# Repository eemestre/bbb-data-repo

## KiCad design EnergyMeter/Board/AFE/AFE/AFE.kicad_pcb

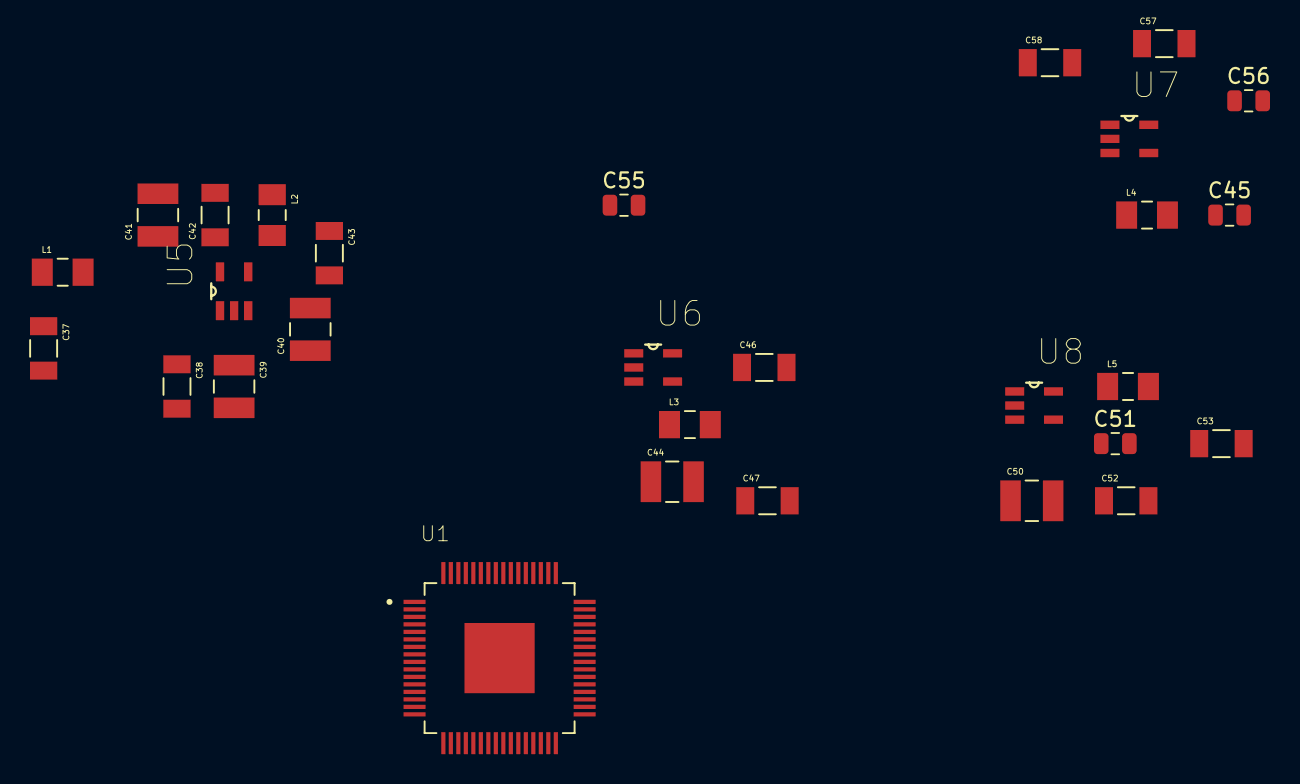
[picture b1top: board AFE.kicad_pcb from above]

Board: 2 copper layers, 29 parts (0 on the bottom side), 13 nets, no tracks yet.

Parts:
C37, C38, C42, C43, C46, C47, C52, C53, C57, C58: 10UF; CAPC3216X180N
C39, C40, C41, C44, C50: 1UF; CAPC3225X210N
C45, C51, C55, C56: 2.2UF; C_0805_2012Metric
L1, L2, L3, L4, L5: 470UH; BEADC3216X180N
U1: ADC; QFP50P1200X1200X120-65N
U5: TPS60403DBVT; SOT95P280X145-5N
U6: TPS73230DBVT; SOT95P280X145-5N
U7: TPS72301DBVT; SOT95P280X145-5N
U8: TPS73201DBVT; SOT95P280X145-5N

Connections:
+5V: C37.1, L1.1
GNDA: C37.2, C38.2, C39.2, C41.2, C42.2, C43.2, C44.2, C45.2, C46.2, C47.2, C51.2, C52.2, C53.2, C55.2, C56.2, C57.2, C58.2, U5.4, U6.2, U7.1, U8.2
unnamed: C38.1, C39.1, C44.1, C50.1, L1.2, U5.2, U6.1, U6.3, U8.1, U8.3
unnamed: C40.1, U5.3
unnamed: C40.2, U5.5
unnamed: C41.1, C42.1, L2.1, U5.1
unnamed: C45.1, C46.1, L3.1, U6.5
unnamed: C51.1, C52.1, L5.1, U8.5
unnamed: C56.1, C57.1, L4.1
TP4: C43.1, C55.1, L2.2, U7.2, U7.3
TP5: C47.1, L3.2
TP6: C58.1, L4.2
TP13: C53.1, L5.2

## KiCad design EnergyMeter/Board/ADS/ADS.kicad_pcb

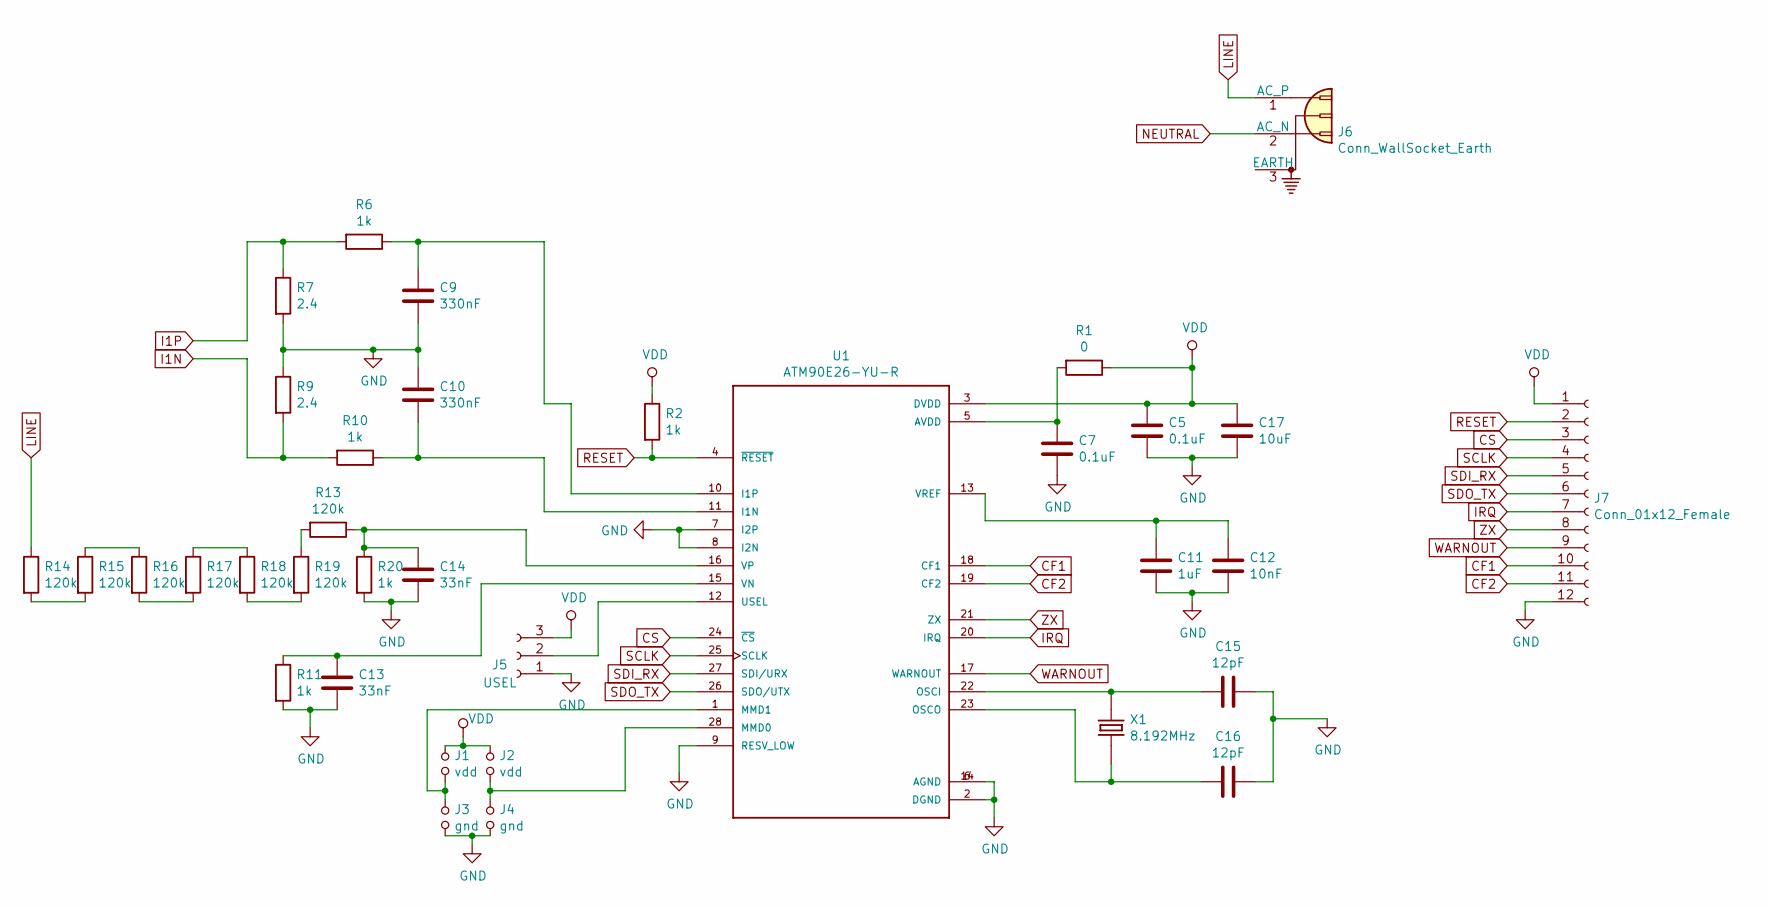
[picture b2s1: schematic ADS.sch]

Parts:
C5, C7: 0.1uF; C_0603_1608Metric
C9, C10: 330nF; C_0603_1608Metric
C11: 1uF; C_0603_1608Metric
C12: 10nF; C_0603_1608Metric
C13, C14: 33nF; C_0603_1608Metric
C15, C16: 12pF; C_0603_1608Metric
C17: 10uF; C_0603_1608Metric
J1, J2: vdd; PinHeader_1x02_P2.54mm_Vertical
J3, J4: gnd; PinHeader_1x02_P2.54mm_Vertical
J5: USEL; PinHeader_1x03_P2.54mm_Vertical
J6: Conn_WallSocket_Earth
J7: Conn_01x12_Female; PinHeader_1x12_P2.54mm_Vertical
R1: 0; R_0603_1608Metric
R2, R6, R10, R11, R20: 1k; R_0603_1608Metric
R7, R9: 2.4; R_0603_1608Metric
R13, R14, R15, R16, R17, R18, R19: 120k; R_0805_2012Metric
U1: ATM90E26-YU-R; SOP65P780X200-28N
X1: 8.192MHz; XTAL_ECS-40-18-5PXEN-TR

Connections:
CF1: J7.10, U1.18 (CF1)
CF2: J7.11, U1.19 (CF2)
CS: J7.3, U1.24 (~CS~)
I1N: R9.2, R10.2
I1P: R6.2, R7.1
IRQ: J7.7, U1.20 (IRQ)
LINE: J6.1 (AC_P), R14.1
NEUTRAL: J6.2 (AC_N)
unnamed: C7.1, R1.2, U1.5 (AVDD)
unnamed: C9.1, R6.1, U1.10 (I1P)
unnamed: C10.2, R10.1, U1.11 (I1N)
unnamed: C11.1, C12.1, U1.13 (VREF)
unnamed: C13.1, R11.1, U1.15 (VN)
unnamed: C14.1, R13.1, R20.1, U1.16 (VP)
unnamed: C15.2, U1.22 (OSCI), X1.1
unnamed: C16.2, U1.23 (OSCO), X1.2
unnamed: J1.2, J3.1, U1.1 (MMD1)
unnamed: J2.2, J4.1, U1.28 (MMD0)
unnamed: J5.2, U1.12 (USEL)
unnamed: R13.2, R19.1
unnamed: R14.2, R15.2
unnamed: R15.1, R16.1
unnamed: R16.2, R17.2
unnamed: R17.1, R18.1
unnamed: R18.2, R19.2
RESET: J7.2, R2.2, U1.4 (~RESET~)
SCLK: J7.4, U1.25 (SCLK)
SDI_RX: J7.5, U1.27 (SDI/URX)
SDO_TX: J7.6, U1.26 (SDO/UTX)
VDD: C5.1, C17.1, J1.1, J2.1, J5.3, J7.1, R1.1, R2.1, U1.3 (DVDD)
WARNOUT: J7.9, U1.17 (WARNOUT)
ZX: J7.8, U1.21 (ZX)

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
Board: 2 copper layers, 35 parts (0 on the bottom side), 33 nets, no tracks yet.

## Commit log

2024-10-23 first plot.png
2024-10-23 Codes and second plot
2024-10-23 third png
2024-10-23 png 4
2024-10-24 atualizacao
2024-11-19 teste
2024-11-19 teste 2
2024-11-19 testee
2024-11-19 teste 3
2024-11-19 teste 4
2025-04-11 tirando os plot.png
2025-05-21 fix: organizei arquivos em pastas e criei rb_file.c
2025-05-21 fix: rm arquivos errados
2025-06-13 energy meter
2025-06-13 gitignore
